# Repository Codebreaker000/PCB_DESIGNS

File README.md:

# PCB_DESIGNS

Contains all PCB designs with Schematics and Board view file's and both pdf's to understand and gerber files and the view and layout of the PCB's.

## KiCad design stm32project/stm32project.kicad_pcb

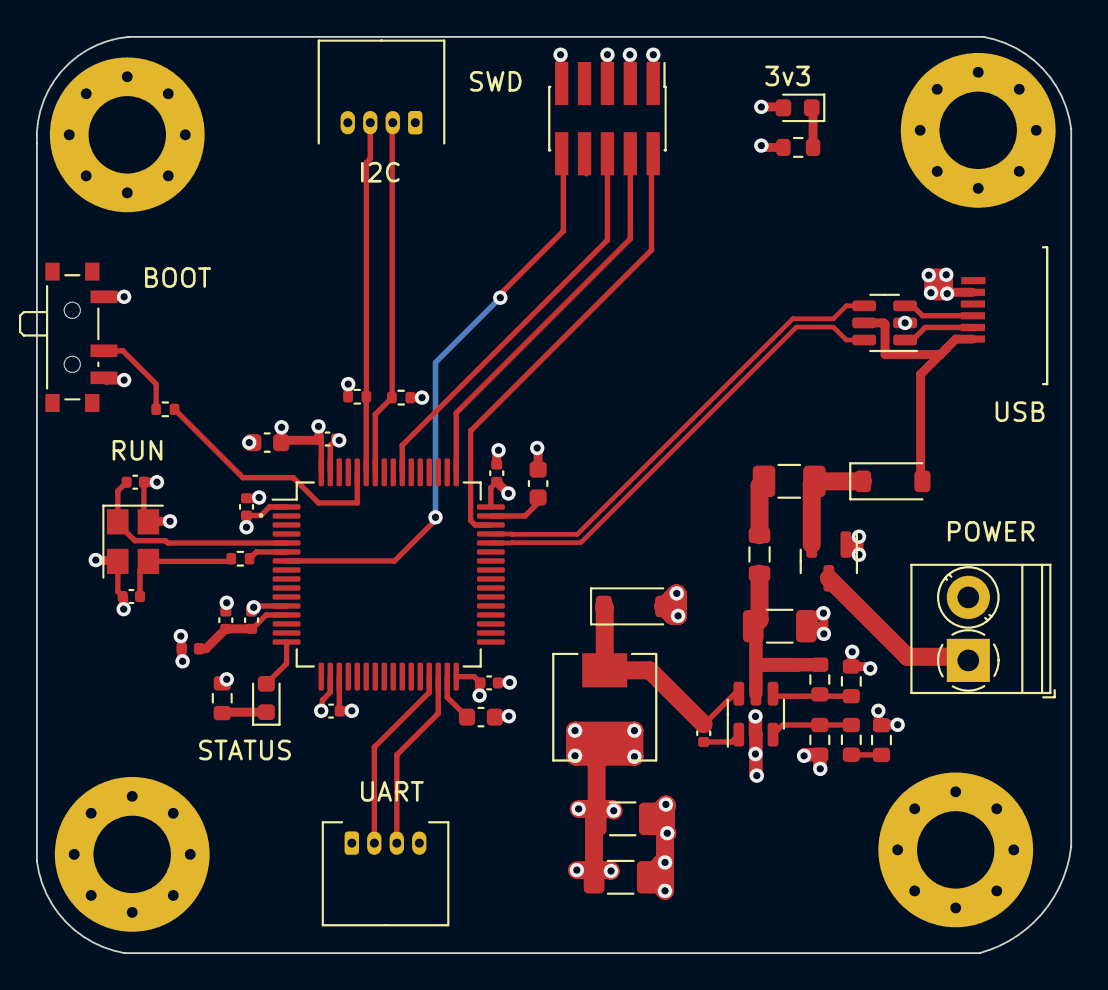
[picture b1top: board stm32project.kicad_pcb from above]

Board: 4 copper layers, 57.5 x 50.9 mm, 50 parts (0 on the bottom side), 35 nets.

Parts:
C1, C2: 2u2; C_0603_1608Metric
C3: 4u7; C_0603_1608Metric
C4, C5, C6, C7, C8: 100n; C_0402_1005Metric
C9, C16, C17: 10u; C_1206_3216Metric
C10: 1u; C_0402_1005Metric
C11, C15: 10n; C_0402_1005Metric
C12, C13: 12P; C_0402_1005Metric
D1: BLUE; LED_0603_1608Metric
D2, D3: B5819W; D_SOD-123
D4: RED; LED_0603_1608Metric
F1: 250mA; Fuse_1206_3216Metric
FB1: 600 @600MHz; L_0805_2012Metric
H1, H2, H3, H4: MountingHole_Pad; MountingHole_4.3mm_M4_Pad_Via
J1: Screw_Terminal_01x02; TerminalBlock_Phoenix_PT-1,5-2-3.5-H_1x02_P3.50mm_Horizontal
J2: SWD; PinHeader_2x05_P1.27mm_Vertical_SMD
J3, J4: Conn_01x04; Molex_PicoBlade_53048-0410_1x04_P1.25mm_Horizontal
J5: USB_B_Micro; AMPHENOL_10118193-0001LF (1)
L1: 39n; L_0402_1005Metric
L2: 10U; L_Sunlord_MWSA0518S
Q1: AO3401A; SOT-23
R1: 10k; R_0402_1005Metric
R2: 47; R_0402_1005Metric
R3: 1k5; R_0603_1608Metric
R4: 100k; R_0603_1608Metric
R5: 68k; R_0603_1608Metric
R6: 47K; R_0603_1608Metric
R7: 15K; R_0603_1608Metric
R8: 270K; R_0603_1608Metric
R9, R10: 2k2; R_0402_1005Metric
R11: 1k; R_0603_1608Metric
SW1: SW_SPDT; SW_SPDT_PCM12
U1: STM32F405RGT6; LQFP-64_10x10mm_P0.5mm
U2: SOT-23-6
U3: USBLC6-2SC6; SOT-23-6
Y1: 16MHZ; Crystal_SMD_3225-4Pin_3.2x2.5mm

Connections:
+3.3V: C3.1, C4.1, C5.1, C6.1, C7.1, C8.1, C16.1, C17.1, D4.2 (A), J2.1, J3.1, J4.1, L1.1, L2.2, R6.1, R9.1, R10.1, SW1.1 (A), U1.1 (VBAT), U1.19 (VDD), U1.32 (VDD), U1.48 (VDD), U1.64 (VDD)
+3.3VA: C10.1, C11.1, L1.2, U1.13 (VDDA)
+5V: D3.2 (A), J5.1 (VBUS), U3.5 (VBUS)
+12V: J1.1, Q1.3 (D)
BOOTO: R1.1, U1.60 (BOOT0)
BUCK_BST: C15.1, U2.1 (BST)
BUCK_EN: R4.2, R5.1, U2.4 (EN)
BUCK_FB: R6.2, R7.1, U2.3 (FB)
BUCK_IN: C9.1, FB1.2, R4.1, U2.5 (IN)
BUCK_SW: C15.2, D2.1 (K), L2.1, U2.6 (SW)
GND: C1.2, C2.2, C3.2, C4.2, C5.2, C6.2, C7.2, C8.2, C9.2, C10.2, C11.2, C12.2, C13.2, C16.2, C17.2, D2.2 (A), H1.1, H2.1, H3.1, H4.1, J1.2, J2.3, J2.5, J2.9, J3.4, J4.4, J5.5 (GND), Q1.1 (G), R3.1, R5.2, R8.2, R11.1, SW1.3 (C), U1.12 (VSSA), U1.18 (VSS), U1.63 (VSS), U2.2 (GND), U3.2 (GND), Y1.2, Y1.4
HSE_IN: C12.1, U1.5 (PH0), Y1.1
HSE_OUT: R2.1, U1.6 (PH1)
I2C1_SCL: J4.2, R9.2, U1.58 (PB6)
I2C1_SDA: J4.3, R10.2, U1.59 (PB7)
LED_STATUS: D1.2 (A), U1.16 (PA2)
NRST: J2.10, U1.7 (NRST)
unnamed: C13.1, R2.2, Y1.3
unnamed: D1.1 (K), R3.2
unnamed: D3.1 (K), F1.1, Q1.2 (S)
unnamed: D4.1 (K), R11.2
unnamed: F1.2, FB1.1
unnamed: R7.2, R8.1
unnamed: R1.2, SW1.2 (B)
unnamed: C1.1, U1.31 (VCAP_1)
unnamed: C2.1, U1.47 (VCAP_2)
SWCLK: J2.4, U1.49 (PA14)
SWDIO: J2.2, U1.46 (PA13)
SWO: J2.6, U1.55 (PB3)
USART3_RX: J3.3, U1.30 (PB11)
USART3_TX: J3.2, U1.29 (PB10)
USB_CONN_D+: J5.3 (D+), U3.3 (I/O2)
USB_CONN_D-: J5.2 (D-), U3.1 (I/O1)
USB_D+: U1.45 (PA12), U3.4 (I/O2)
USB_D-: U1.44 (PA11), U3.6 (I/O1)
